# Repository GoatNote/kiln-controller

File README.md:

Kiln Controller
==========

Turns a Raspberry Pi into an inexpensive, web-enabled kiln controller.
PCB is configured for MAX31856 board.

## Features

  * supports [many boards](https://github.com/jbruce12000/kiln-controller/blob/main/docs/supported-boards.md) into addition to raspberry pi
  * supports Adafruit MAX31856 thermocouple boards
  * support for K, J, N, R, S, T, E, or B type thermocouples
  * easy to create new kiln schedules and edit / modify existing schedules
  * no limit to runtime - fire for days if you want
  * view status from multiple devices at once - computer, tablet etc
  * real-time firing cost estimate
  * real-time heating rate displayed in degrees per hour
  * supports PID parameters you tune to your kiln
  * monitors temperature in kiln after schedule has ended
  * api for starting and stopping at any point in a schedule
  * accurate simulation
  * support for shifting schedule when kiln cannot heat quickly enough
  * support for skipping first part of profile to match current kiln temperature
  * prevents integral wind-up when temperatures not near the set point
  * automatic restarts if there is a power outage or other event
  * support for a watcher to page you via slack if you kiln is out of whack
  * easy scheduling of future kiln runs

**Run Kiln Schedule**

**Edit Kiln Schedule**

## Hardware

### Parts

| Image | Hardware | Description |
| ------| -------- | ----------- |
|  | [Raspberry Pi](https://www.adafruit.com/category/105) | Virtually any Raspberry Pi will work since only a few GPIO pins are being used. Any board supported by [blinka](https://circuitpython.org/blinka) and has SPI should work. You'll also want to make sure the board has wifi. If you use something other than a Raspberry PI and get it to work, let me know. |
|  | [Adafruit MAX31855](https://www.adafruit.com/product/269) or [Adafruit MAX31856](https://www.adafruit.com/product/3263) | Thermocouple breakout board |
|  | [Thermocouple](https://www.auberins.com/index.php?main_page=product_info&cPath=20_3&products_id=39) | Invest in a heavy duty, ceramic thermocouple designed for kilns. Make sure the type will work with your thermocouple board. Adafruit-MAX31855 works only with K-type. Adafruit-MAX31856 is flexible and works with many types, but folks usually pick S-type. |
|  | Breadboard | breadboard, ribbon cable, connector for pi's gpio pins & connecting wires |
|  | Solid State Relay | Zero crossing, make sure it can handle the max current of your kiln. Even if the kiln is 220V you can buy a single [3 Phase SSR](https://www.auberins.com/index.php?main_page=product_info&cPath=2_30&products_id=331). It's like having 3 SSRs in one.  Relays this big always require a heat sink. |
|  | Electric Kiln | There are many old electric kilns on the market that don't have digital controls. You can pick one up on the used market cheaply.  This controller will work with 110V or 220V (pick a proper SSR). My kiln is a Skutt KS-1018. |

### Schematic

**WARNING** This project involves high voltages and high currents. Please make sure that anything you build conforms to local electrical codes and aligns with industry best practices.

**Note:** The GPIO configuration in this schematic does not match the defaults, check [config](https://github.com/jbruce12000/kiln-controller/blob/main/config.py) and make sure the gpio pin configuration aligns with your actual connections.

## Software 

### Raspberry PI OS

Download [Raspberry PI OS](https://www.raspberrypi.org/software/). Use Rasberry PI Imaging tool to install the OS on an SD card. Boot the OS, open a terminal and...

    $ sudo apt-get update
    $ sudo apt-get dist-upgrade
    $ git clone https://github.com/jbruce12000/kiln-controller
    $ cd kiln-controller
    $ python3 -m venv venv
    $ source venv/bin/activate
    $ pip install -r requirements.txt

*Note: The above steps work on ubuntu if you prefer*

### Raspberry PI deployment

If you're done playing around with simulations and want to deploy the code on a Raspberry PI to control a kiln, you'll need to do this in addition to the stuff listed above:

    $ sudo raspi-config
    interfacing options -> SPI -> Select Yes to enable
    select reboot

## Configuration

All parameters are defined in config.py. You need to read through config.py carefully to understand each setting. Here are some of the most important settings:

| Variable | Default | Description |
| -------- | ------- | ----------- |
| sensor_time_wait | 2 seconds | It's the duty cycle for the entire system.  It's set to two seconds by default which means that a decision is made every 2s about whether to turn on relay[s] and for how long. If you use mechanical relays, you may want to increase this. At 2s, my SSR switches 11,000 times in 13 hours. |
| temp_scale | f | f for farenheit, c for celcius |
| pid parameters | | Used to tune your kiln. See PID Tuning. |
| simulate | True | Simulate a kiln. Used to test the software by new users so they can check out the features. |

## Testing

After you've completed connecting all the hardware together, there are scripts to test the thermocouple and to test the output to the solid state relay. Read the scripts below and then start your testing. First, activate the virtual environment like so...

     $ source venv/bin/activate

then test the thermocouple with:

     $ ./test-thermocouple.py

then test the output with:

     $ ./test-output.py

and you can use this script to examine each pin's state including input/output/voltage on your board:

     $ ./gpioreadall.py

## PID Tuning

Run the [autotuner](https://github.com/jbruce12000/kiln-controller/blob/main/docs/ziegler_tuning.md). It will heat your kiln to 400F, pass that, and then once it cools back down to 400F, it will calculate PID values which you must copy into config.py. No tuning is perfect across a wide temperature range. Here is a [PID Tuning Guide](https://github.com/jbruce12000/kiln-controller/blob/main/docs/pid_tuning.md) if you end up having to manually tune.

There is a state view that can help with tuning. It shows the P,I, and D parameters over time plus allows for a csv dump of data collected. It also shows lots of other details that might help with troubleshooting issues. Go to /state.

## Usage

### Server Startup

    $ source venv/bin/activate; ./kiln-controller.py

### Autostart Server onBoot
If you want the server to autostart on boot, run the following command:

    $ /home/pi/kiln-controller/start-on-boot

### Client Access

Click http://127.0.0.1:8081 for local development or the IP
of your PI and the port defined in config.py (default 8081).

### Simulation

In config.py, set **simulate=True**. Start the server and select a profile and click Start. Simulations run at near real time.

### Scheduling a Kiln run

If you want to schedule a kiln run to start in the future. Here are [examples](https://github.com/jbruce12000/kiln-controller/blob/main/docs/scheduling.md).

### Watcher

If you're busy and do not want to sit around watching the web interface for problems, there is a watcher.py script which you can run on any machine in your local network or even on the raspberry pi which will watch the kiln-controller process to make sure it is running a schedule, and staying within a pre-defined temperature range. When things go bad, it sends messages to a slack channel you define. I have alerts set on my android phone for that specific slack channel. Here are detailed [instructions](https://github.com/jbruce12000/kiln-controller/blob/main/docs/watcher.md).

## License

This program is free software: you can redistribute it and/or modify
it under the terms of the GNU General Public License as published by
the Free Software Foundation, either version 3 of the License, or
(at your option) any later version.

This program is distributed in the hope that it will be useful,
but WITHOUT ANY WARRANTY; without even the implied warranty of
MERCHANTABILITY or FITNESS FOR A PARTICULAR PURPOSE.  See the
GNU General Public License for more details.

You should have received a copy of the GNU General Public License
along with this program.  If not, see <http://www.gnu.org/licenses/>.

## Support & Contact

Please use the issue tracker for project related issues.
If you're having trouble with hardware, I did too.  Here is a [troubleshooting guide](https://github.com/jbruce12000/kiln-controller/blob/main/docs/troubleshooting.md) I created for testing RPi gpio pins.

## Origin
This project was originally forked from https://github.com/apollo-ng/picoReflow but has diverged a large amount.

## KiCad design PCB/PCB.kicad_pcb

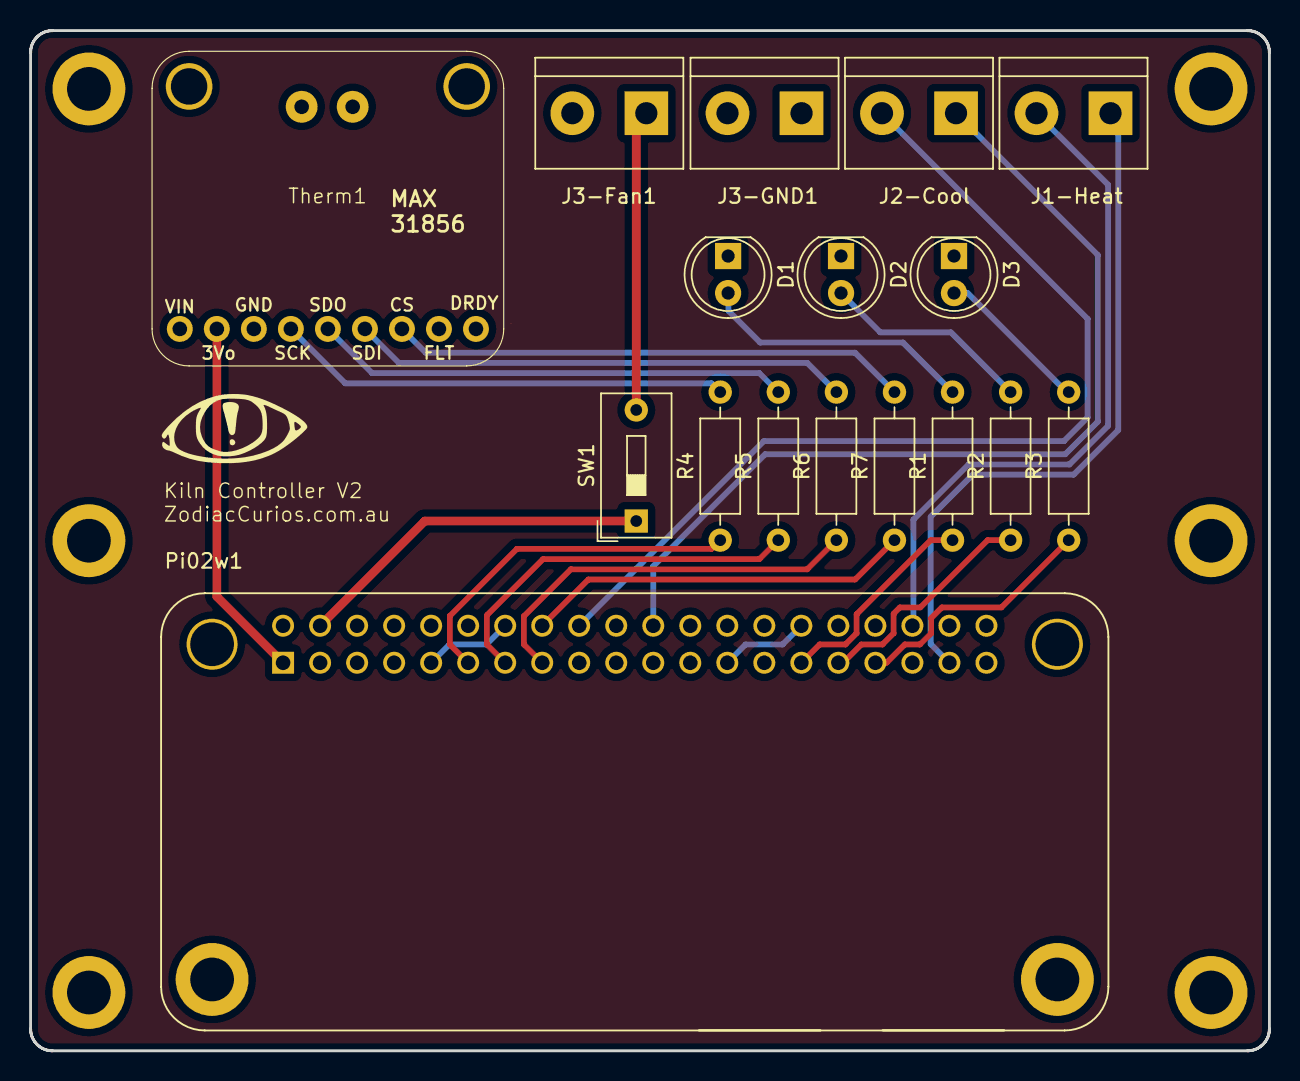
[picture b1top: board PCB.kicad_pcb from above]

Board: 2 copper layers, 85.0 x 70.0 mm, 17 parts (0 on the bottom side), 22 nets.

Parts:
D1, D2, D3: LED; LED_D5.0mm
J1-Heat, J2-Cool, J3-Fan1, J3-GND1: Screw_Terminal_01x02; TerminalBlock_bornier-2_P5.08mm
Pi02w1: SC1176; MODULE_SC1176
R1, R2, R3, R4, R5, R6, R7: R; R_Axial_DIN0207_L6.3mm_D2.5mm_P10.16mm_Horizontal
SW1: SW_SPST; SW_DIP_SPSTx01_Slide_9.78x4.72mm_W7.62mm_P2.54mm
Therm1: MAX31856

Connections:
GND: D1.1 (K), D2.1 (K), D3.1 (K), J3-Fan1.2, J3-GND1.1, J3-GND1.2, Pi02w1.6 (GND_6), Pi02w1.9 (GND_9), Pi02w1.14 (GND_14), Pi02w1.20 (GND_20), Pi02w1.25 (GND_25), Pi02w1.30 (GND_30), Pi02w1.34 (GND_34), Pi02w1.39 (GND_39), Therm1.7
unnamed: D1.2 (A), R1.2
unnamed: D2.2 (A), R2.2
unnamed: D3.2 (A), R3.2
unnamed: J1-Heat.1, Pi02w1.37 (GPIO26)
unnamed: J1-Heat.2, Pi02w1.36 (GPIO16)
unnamed: J2-Cool.1, Pi02w1.22 (GPIO25/GPIO_GEN6)
unnamed: J2-Cool.2, Pi02w1.18 (GPIO24/GPIO_GEN5)
unnamed: J3-Fan1.1, SW1.2 (B)
unnamed: Pi02w1.1 (3V3_1), Therm1.8
unnamed: Pi02w1.4 (5V_4), SW1.1 (A)
unnamed: Pi02w1.29 (GPIO5), R1.1
unnamed: Pi02w1.31 (GPIO6), R2.1
unnamed: Pi02w1.33 (GPIO13), R3.1
unnamed: Pi02w1.11 (GPIO17/GPIO_GEN0), R4.1
unnamed: Pi02w1.15 (GPIO22/GPIO_GEN3), R6.1
unnamed: Pi02w1.16 (GPIO23/GPIO_GEN4), R7.1
unnamed: Pi02w1.13 (GPIO27/GPIO_GEN2), R5.1
unnamed: R4.2, Therm1.6
unnamed: R5.2, Therm1.5
unnamed: R6.2, Therm1.4
unnamed: R7.2, Therm1.3

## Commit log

2025-07-17 finally backing up my changes >.<
2026-05-17 PCB for ease of assembly
